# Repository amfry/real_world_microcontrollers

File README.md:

# Real Wold Microcontrollers - Low Power Current Logger
###### This project was completed as part of Microcontrollers for the Real World at Olin College of Engineering, Fall 2020
## Description
This board was designed to assist the [ADE Air Partners](https://www.airpartners.org/) team in evaluating how [HEPA air purifiers](https://austinair.com/shop/healthmate/) are being used by residents in East Boston. The purifiers provided the most health benefits when used 24/7 at the highest setting.  However, when deployed, purifiers are often turned to a lower setting or unplugged by users. To evalute user behavior, the board logs current continously over an extended duration.

The purifier has 4 modes have distinct current requirements, making a current logger a simple way to gain valuable data about purifier usage.  The logger was designed to be battery operated to allow data to be logged discretely.  making it low power means that data can be collected over an extended period of time. During devlopment of the board, when there was no immediate access to an air purifer, the board was tested on a standard hair dryer. The data from a test with the hair dryer can be seen below.  
%20vs.%20Time.png)  
### Requirments
The low power currentl logger was designed to met the following technical requirments:
- Sense current running through a wall power cable.
- Keep accurate time to sync logged data with other data streams.
- Write current values and necessary time stamps to an SD card.
- Run off of battery power for a minimum of 4 weeks.

The battery pack on the board supplies 5200 mA hours and after measuring the current used while the board is logging, the board should last 57 days and weeks assuming a nominal current of 3.78 mA when the sample rate every 5 minutes.
## Design
### Schematic
The board layout has 7 major components:
- [Processor](https://www.sparkfun.com/products/11114): The arduino mini pro 3.3v was chosen because it was compatible with the power requirments of the other module that were being selected. It's low clock speed makes it a good canidate for this low power project and the DIY intrnet community has used in extensively in data logging projects.
  
- [RTC](https://www.adafruit.com/product/3013): The DS3231 is a precise RTC with it's own battery and a temperature sensor to to compensate for crsyal frequency changes as the temperature changes. It communicates with the processor over I2C. In this application, the time is set at compile time using the arduino IDE's compiler.  
  
- [SD Card module](https://www.sparkfun.com/products/544): This simple micro-SD module works over SPI and was easier to solder to the board the breakout rather than wokring with the raw socket.  
  
- [Display module](https://www.adafruit.com/product/4440#technical-details): This display module communicated over I2C and it's relatively small screen was sufficient for creating a minimal user interface to display the set time, status of the SD, and battery levels during module intergration.  
  
- [Buck/Boost Converter](https://www.sparkfun.com/products/15208) This board was choosen due to it's high efficieny at providing a constant 3.3 input voltage. In the board, this is connected to 2 18650 batteries that are in parallel to make up the power source for the project.  
  
- [Current sensor](https://learn.openenergymonitor.org/electricity-monitoring/ct-sensors/yhdc-sct-013-000-ct-sensor-report) The SCT013 sensor is able to log current data without having to slice any wire and comes with it's own arduino library to process that analog signal which made it a good pick for this project.

The schematic and board designed were completed in KiCAD and can be see [here](https://github.com/amfry/real_world_microcontrollers/blob/main/hardware/low_current_data_logger.zip).  
### Board
Below is the populated final version of the low power current logger. The board was manufactured by [JLCPCB](https://jlcpcb.com/) and was assembled with hand soldereding.  The board is 2-layer with all THT componenets. The board layout and assembly can be seen below.  

### BOM & Cost
A motivation for designing this board for the [ADE Air Partners](https://www.airpartners.org/) team was to create a lower cost alternative to the current products used for current data logging. Products that can do that such as a [HOBO data logger](https://www.onsetcomp.com/products/data-loggers/ux120-006m/), but these products are bulky, expensive (> $200 each), and generally designed for industrial applications. This means that the baord developed could save the team over a 100 dollars for each logging unit. Additional cost reduction could be implemnted such as transition to using just the processor chip in the arduino mini pro and manufacturing the board in bulk.  

### Next Steps
To improve the utility of this board for it's inteded purpose further development is need.
- User interface: The board has a display and push button user interface that are not currently being used. In doing software development, the large size of the display library made the display difficult to integrate with other core functionality. More research and development into how to implemnt display functionality with low memory avaliable is needed.
- Low power improvments: While the board could run for ~57 days many amount of time with the current battery pack and software, extending the battery life of the board would allow more holistic data to be collected on air purifer usage. Implemnting "sleep mode" in between data samples and expanding the battery pack should be complete to imporve the board.
###### Special thanks to Stan Reifiel for his guidance throughout this project.

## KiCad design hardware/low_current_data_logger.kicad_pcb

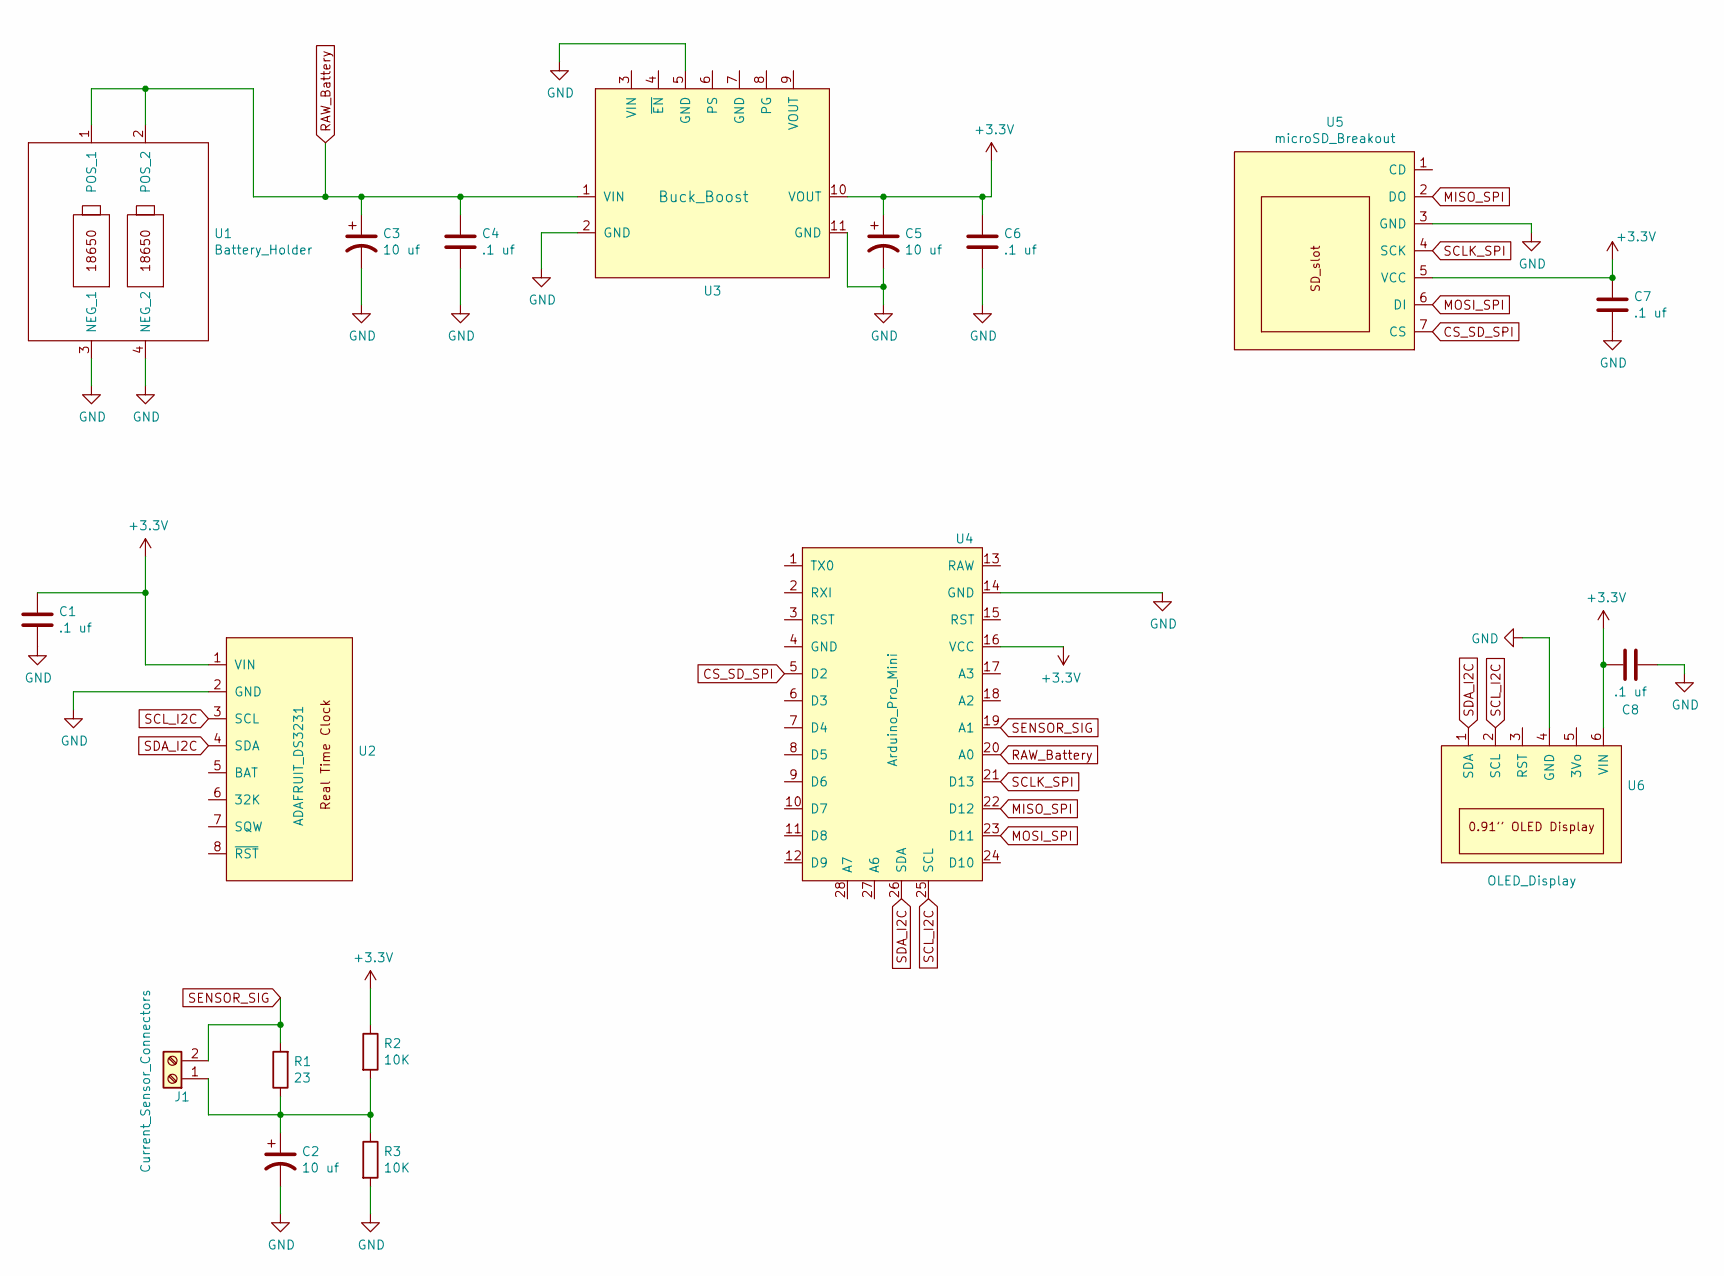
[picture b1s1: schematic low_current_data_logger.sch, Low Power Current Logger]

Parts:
C1, C4, C6, C7, C8: .1 uf; C_Disc_D4.7mm_W2.5mm_P5.00mm
C2, C3, C5: 10 uf; CP_Radial_Tantal_D4.5mm_P2.50mm
J1: Current_Sensor_Connectors; TerminalBlock_4Ucon_1x02_P3.50mm_Vertical
R1: 23; resistor_THT
R2, R3: 10K; resistor_THT
U1: Battery_Holder; 36-1049-ND
U2: ADAFRUIT_DS3231; adafruit_RTC
U3: Buck_Boost; buck_boost
U4: Arduino_Pro_Mini; arduino_mini_pro
U5: microSD_Breakout; sd_mod
U6: OLED_Display; oled_display

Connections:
+3V3: C1.1, C5.1, C6.1, C7.1, C8.1, R2.1, U2.1 (VIN), U3.10 (VOUT), U4.16 (VCC), U5.5 (VCC), U6.6 (VIN)
CS_SD_SPI: U4.5 (D2), U5.7 (CS)
GND: C1.2, C2.2, C3.2, C4.2, C5.2, C6.2, C7.2, C8.2, R3.2, U1.3 (NEG_1), U1.4 (NEG_2), U2.2 (GND), U3.2 (GND), U3.5 (GND), U3.11 (GND), U4.14 (GND), U5.3 (GND), U6.4 (GND)
MISO_SPI: U4.22 (D12), U5.2 (DO)
MOSI_SPI: U4.23 (D11), U5.6 (DI)
unnamed: C2.1, J1.1, R1.1, R2.2, R3.1
RAW_Battery: C3.1, C4.1, U1.1 (POS_1), U1.2 (POS_2), U3.1 (VIN), U4.20 (A0)
SCLK_SPI: U4.21 (D13), U5.4 (SCK)
SCL_I2C: U2.3 (SCL), U4.25 (SCL), U6.2 (SCL)
SDA_I2C: U2.4 (SDA), U4.26 (SDA), U6.1 (SDA)
SENSOR_SIG: J1.2, R1.2, U4.19 (A1)

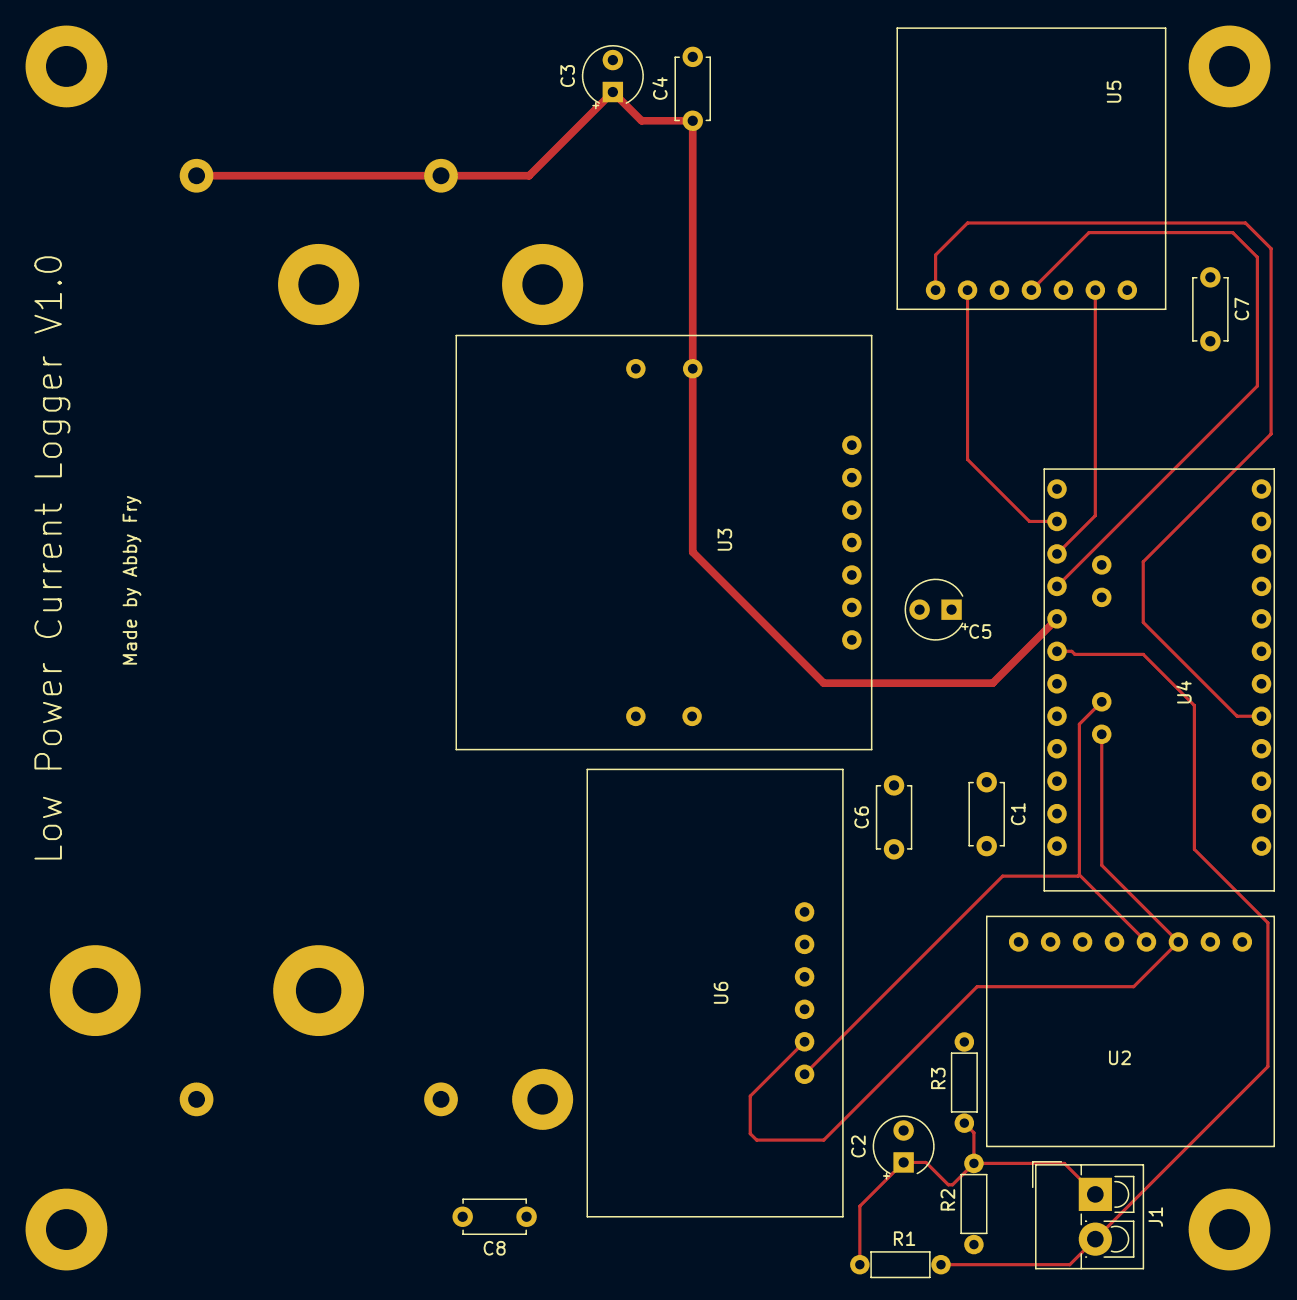
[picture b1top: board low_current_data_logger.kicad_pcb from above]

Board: 4 copper layers, 18 parts (1 on the bottom side), 11 nets.

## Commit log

2020-11-15 adding test script
2020-12-15 cleaning up
2020-12-15 adding hardware files
